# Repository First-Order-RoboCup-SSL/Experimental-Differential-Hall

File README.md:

# Experimental-Differential-Hall

PCB files for an experimental differential (dual) Hall element sensor. This PCB will attach to an STM32 which will perform processing on the output signals, so this PCB takes the Hall elements' output and ensures that the swing will use the maximum part of the 0-3V3 the STM32 can accept for SNR.

Still need to minimise resistors and power usage around our 5(?)% tolerance for resistors and then route PCB, but the amplifier (assuming $\pm$ 370mV around "ground" (2V) seems to work in LTSpice.

Takes in 3V3, GND, and 5V because the Hall element AFAIK wants $\pm$ 2V around "GND".

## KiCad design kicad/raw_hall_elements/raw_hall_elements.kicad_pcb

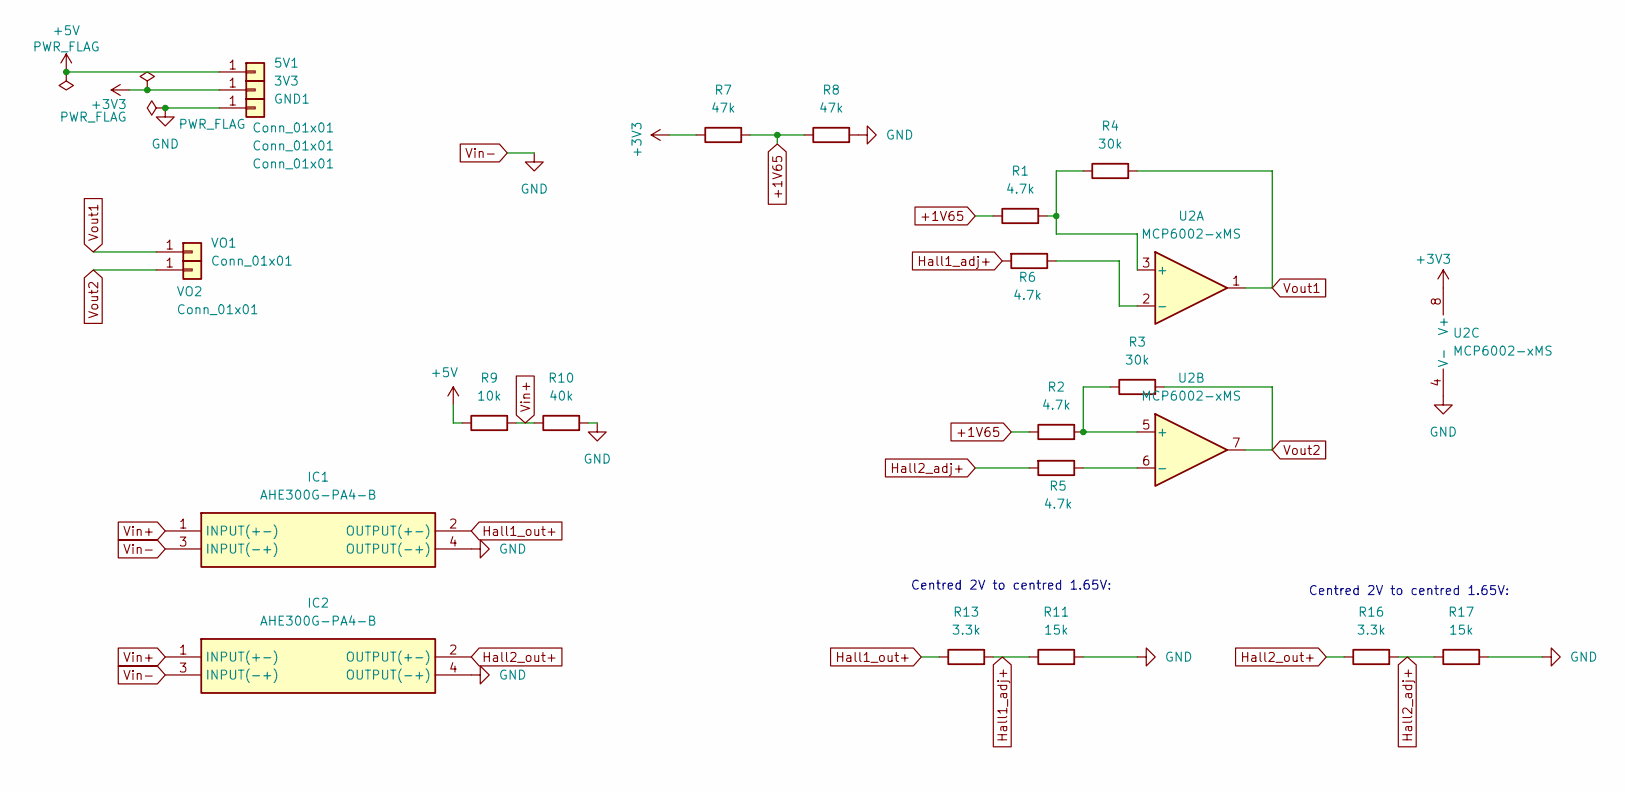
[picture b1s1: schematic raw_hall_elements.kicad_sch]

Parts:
3V3, 5V1: Conn_01x01; TestPoint_THTPad_1.5x1.5mm_Drill0.7mm
GND1: Conn_01x01; TestPoint_THTPad_1.5x1.5mm_Drill0.7mm
IC1, IC2: AHE300G-PA4-B; AHE300GPA4B; Manufacturer_Part_Number AHE300G-PA4-B
R1, R2, R5, R6: 4.7k; R_0603_1608Metric
R3, R4: 30k; R_0603_1608Metric
R7, R8: 47k; R_0603_1608Metric
R9: 10k; R_0603_1608Metric
R10: 40k; R_0603_1608Metric
R11, R17: 15k; R_0603_1608Metric
R13, R16: 3.3k; R_0603_1608Metric
U2: MCP6002-xMS; MSOP-8_3x3mm_P0.65mm
VO1, VO2: Conn_01x01; TestPoint_THTPad_1.5x1.5mm_Drill0.7mm

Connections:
+1V65: R1.1, R2.1, R7.2, R8.1
+3V3: 3V3.1, R7.1, U2.8 (V+)
+5V: 5V1.1, R9.1
Hall1_adj+: R6.2, R11.1, R13.2
Hall1_out+: IC1.2 (OUTPUT(+-)), R13.1
Hall2_adj+: R5.2, R16.2, R17.1
Hall2_out+: IC2.2 (OUTPUT(+-)), R16.1
unnamed: R1.2, R4.1, U2.3 (+)
unnamed: R6.1, U2.2 (-)
unnamed: R2.2, R3.1, U2.5 (+)
unnamed: R5.1, U2.6 (-)
Vin+: IC1.1 (INPUT(+-)), IC2.1 (INPUT(+-)), R9.2, R10.1
Vin-: GND1.1, IC1.3 (INPUT(-+)), IC1.4 (OUTPUT(-+)), IC2.3 (INPUT(-+)), IC2.4 (OUTPUT(-+)), R8.2, R10.2, R11.2, R17.2, U2.4 (V-)
Vout1: R4.2, U2.1, VO1.1
Vout2: R3.2, U2.7, VO2.1

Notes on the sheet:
Centred 2V to centred 1.65V:

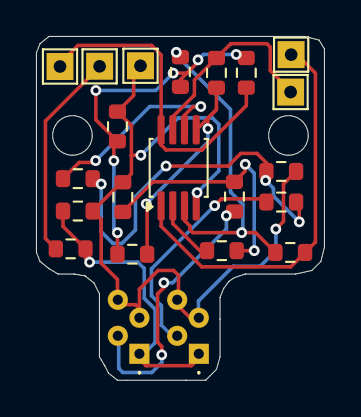
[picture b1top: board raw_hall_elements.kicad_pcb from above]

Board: 2 copper layers, 16.0 x 19.1 mm, 22 parts (0 on the bottom side), 15 nets.

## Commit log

2025-11-19 initial with current kicad work
2025-11-19 Clean ignored files
2025-11-19 LaTeX exists
2025-12-18 Schematic now uses smaller opamp
2025-12-23 more progress
2025-12-23 more progress 2
2025-12-24 one more trace ahhhhh
2025-12-25 schematic clean up and layout finalise
2025-12-27 clean up schematic, finish layout and sent for manuf
